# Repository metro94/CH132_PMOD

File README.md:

# CH132_PMOD: Dual PMOD module for WCH CH132H (USB PHY)

Used for testing WCH CH132H. Test passed for Lattice ECP5 FPGA.

Compatible with Digilent PMOD specification (300 mil apart).

The trace lengths of ULPI signals are **NOT** the same. It's not that it can't be used, right?

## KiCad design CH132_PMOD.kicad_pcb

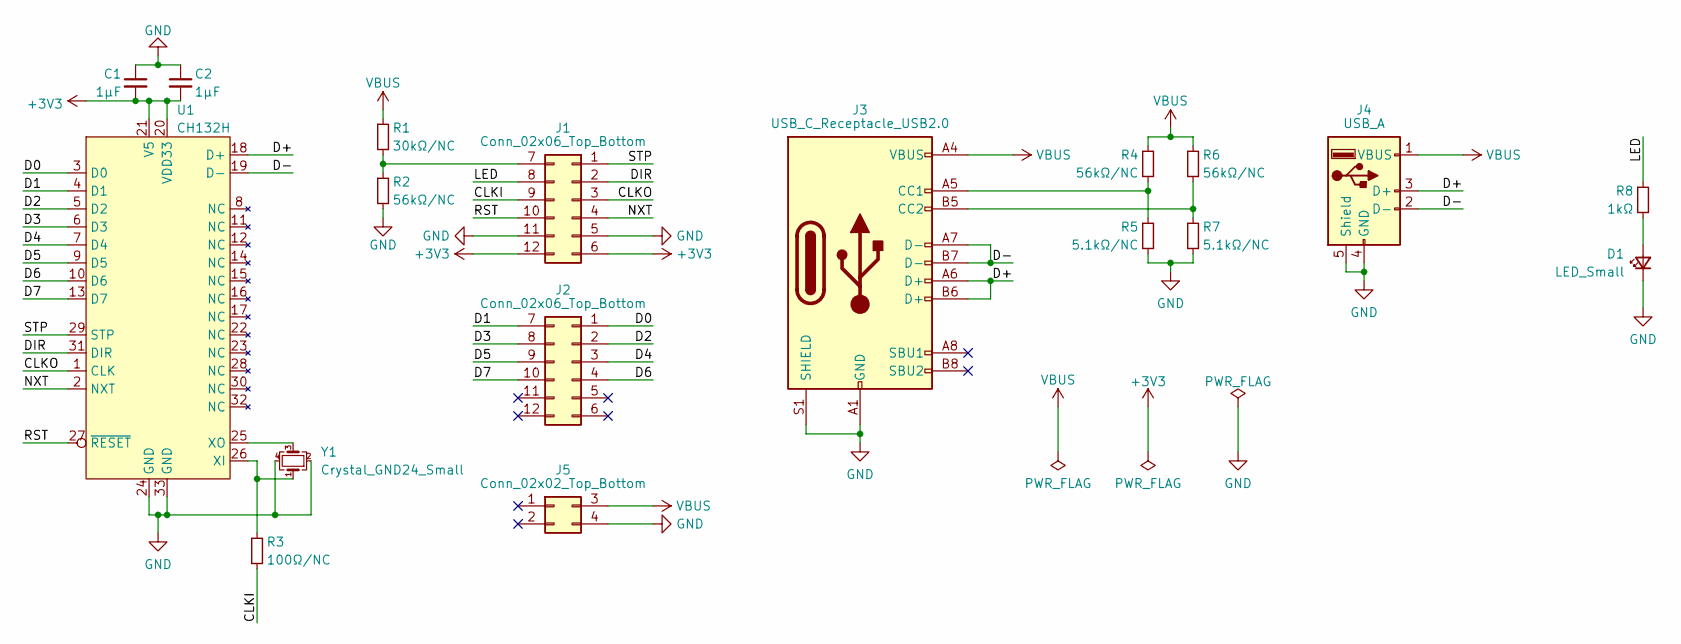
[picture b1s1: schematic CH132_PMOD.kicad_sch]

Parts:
C1, C2: 1μF; C_0805_2012Metric_Pad1.18x1.45mm_HandSolder
D1: LED_Small; LED_0805_2012Metric_Pad1.15x1.40mm_HandSolder
J1, J2: Conn_02x06_Top_Bottom; Pmod_Dual
J3: USB_C_Receptacle_USB2.0; USB_C_Receptacle_HRO_TYPE-C-31-M-12
J4: USB_A; USB_A_CONNFLY_DS1095-WNR0
J5: Conn_02x02_Top_Bottom; EdgePads_01x02_Open
R1: 30kΩ/NC; R_0805_2012Metric_Pad1.20x1.40mm_HandSolder
R2, R4, R6: 56kΩ/NC; R_0805_2012Metric_Pad1.20x1.40mm_HandSolder
R3: 100Ω/NC; R_0805_2012Metric_Pad1.20x1.40mm_HandSolder
R5, R7: 5.1kΩ/NC; R_0805_2012Metric_Pad1.20x1.40mm_HandSolder
R8: 1kΩ; R_0805_2012Metric_Pad1.20x1.40mm_HandSolder
U1: CH132H; QFN-32-1EP_5x5mm_P0.5mm_EP3.3x3.3mm
Y1: Crystal_GND24_Small; Crystal_SMD_SeikoEpson_TSX3225-4Pin_3.2x2.5mm_HandSoldering

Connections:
+3V3: C1.2, C2.2, J1.6, J1.12, U1.20 (VDD33), U1.21 (V5)
/CLKI: J1.9, R3.2
/CLKO: J1.3, U1.1 (CLK)
/D0: J2.1, U1.3 (D0)
/D1: J2.7, U1.4 (D1)
/D2: J2.2, U1.5 (D2)
/D3: J2.8, U1.6 (D3)
/D4: J2.3, U1.7 (D4)
/D5: J2.9, U1.9 (D5)
/D6: J2.4, U1.10 (D6)
/D7: J2.10, U1.13 (D7)
/D+: J3.A6 (D+), J3.B6 (D+), J4.3 (D+), U1.18 (D+)
/D-: J3.A7 (D-), J3.B7 (D-), J4.2 (D-), U1.19 (D-)
/DIR: J1.2, U1.31 (DIR)
/LED: J1.8, R8.1
/NXT: J1.4, U1.2 (NXT)
/RST: J1.10, U1.27 (~RESET)
/STP: J1.1, U1.29 (STP)
GND: C1.1, C2.1, D1.1 (K), J1.5, J1.11, J3.A1 (GND), J3.A12 (GND), J3.B1 (GND), J3.B12 (GND), J3.S1 (SHIELD), J4.4 (GND), J4.5 (Shield), J5.4, R2.2, R5.2, R7.2, U1.24 (GND), U1.33 (GND), Y1.2, Y1.4
unnamed: D1.2 (A), R8.2
unnamed: J1.7, R1.2, R2.1
unnamed: J3.A5 (CC1), R4.2, R5.1
unnamed: J3.B5 (CC2), R6.2, R7.1
unnamed: R3.1, U1.26 (XI), Y1.1
unnamed: U1.25 (XO), Y1.3
VBUS: J3.A4 (VBUS), J3.A9 (VBUS), J3.B4 (VBUS), J3.B9 (VBUS), J4.1 (VBUS), J5.3, R1.1, R4.1, R6.1

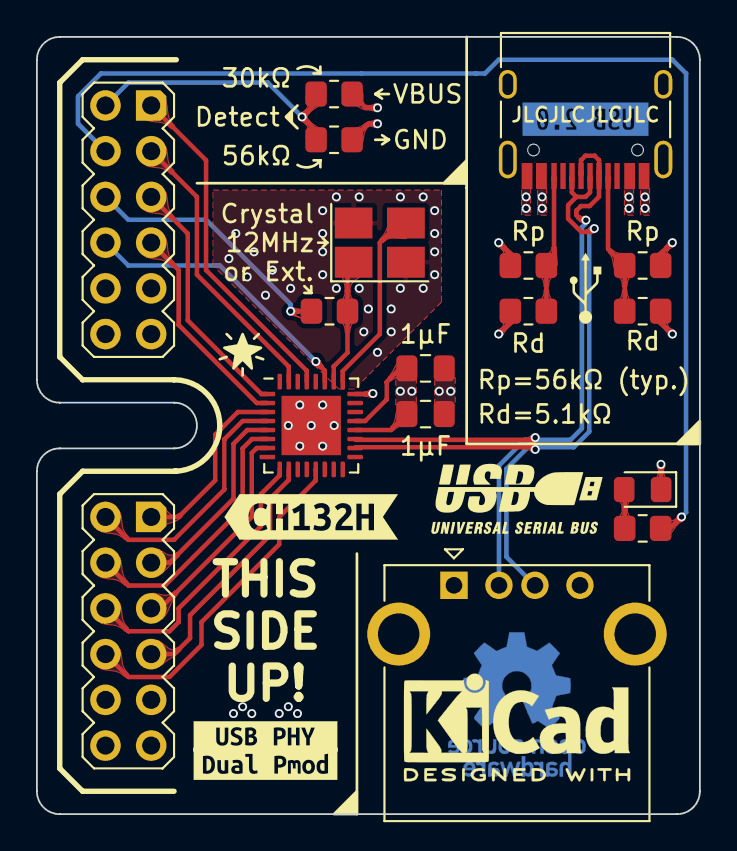
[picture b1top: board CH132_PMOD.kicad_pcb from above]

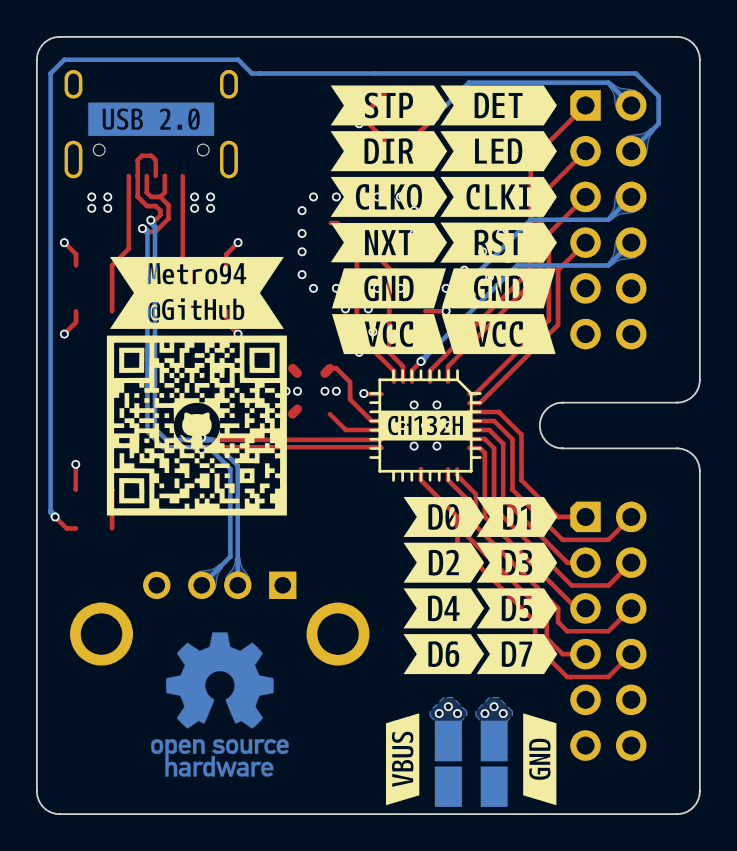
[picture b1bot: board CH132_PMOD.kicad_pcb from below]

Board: 4 copper layers, 36.8 x 43.2 mm, 48 parts (27 on the bottom side), 26 nets.

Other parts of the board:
REF1: KiCad-Logo2_5mm_SilkScreen
REF2: OSHW-Logo_7.5x8mm_Copper
kibuzzard-62DB6A52: G***; kibuzzard-62DB6A52
kibuzzard-62DB6C7E: G***; kibuzzard-62DB6C7E
kibuzzard-62DB6C9E: G***; kibuzzard-62DB6C9E
kibuzzard-62DB6C88: G***; kibuzzard-62DB6C88
kibuzzard-62DB6C95: G***; kibuzzard-62DB6C95
kibuzzard-62DB6D44, kibuzzard-62DB6D44#2: G***; kibuzzard-62DB6D44
kibuzzard-62DB6D54, kibuzzard-62DB6D54#2: G***; kibuzzard-62DB6D54
kibuzzard-62DB6E8D: G***; kibuzzard-62DB6E8D
kibuzzard-62DB6E9D: G***; kibuzzard-62DB6E9D
kibuzzard-62DB6E72: G***; kibuzzard-62DB6E72
kibuzzard-62DB6EAA: G***; kibuzzard-62DB6EAA
kibuzzard-62DB6F6C: G***; kibuzzard-62DB6F6C
kibuzzard-62DB6F17: G***; kibuzzard-62DB6F17
kibuzzard-62DB6F29: G***; kibuzzard-62DB6F29
kibuzzard-62DB6F45: G***; kibuzzard-62DB6F45
kibuzzard-62DB6F50: G***; kibuzzard-62DB6F50
kibuzzard-62DB6F58: G***; kibuzzard-62DB6F58
kibuzzard-62DB6F64: G***; kibuzzard-62DB6F64
kibuzzard-62DB6F73: G***; kibuzzard-62DB6F73
kibuzzard-62DB60FD: G***; kibuzzard-62DB60FD
kibuzzard-62DB724E: G***; kibuzzard-62DB724E
kibuzzard-62DB6272: G***; kibuzzard-62DB6272
kibuzzard-62DB6291: G***; kibuzzard-62DB6291
kibuzzard-62DB7427: G***; kibuzzard-62DB7427
kibuzzard-62DB8401: G***; kibuzzard-62DB8401
kibuzzard-62DB8417: G***; kibuzzard-62DB8417

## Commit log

2022-08-27 add pcb picture
